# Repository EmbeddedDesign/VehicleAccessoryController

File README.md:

# VehicleAccessoryController
Vehicle Dash Cam and Accessory Controller

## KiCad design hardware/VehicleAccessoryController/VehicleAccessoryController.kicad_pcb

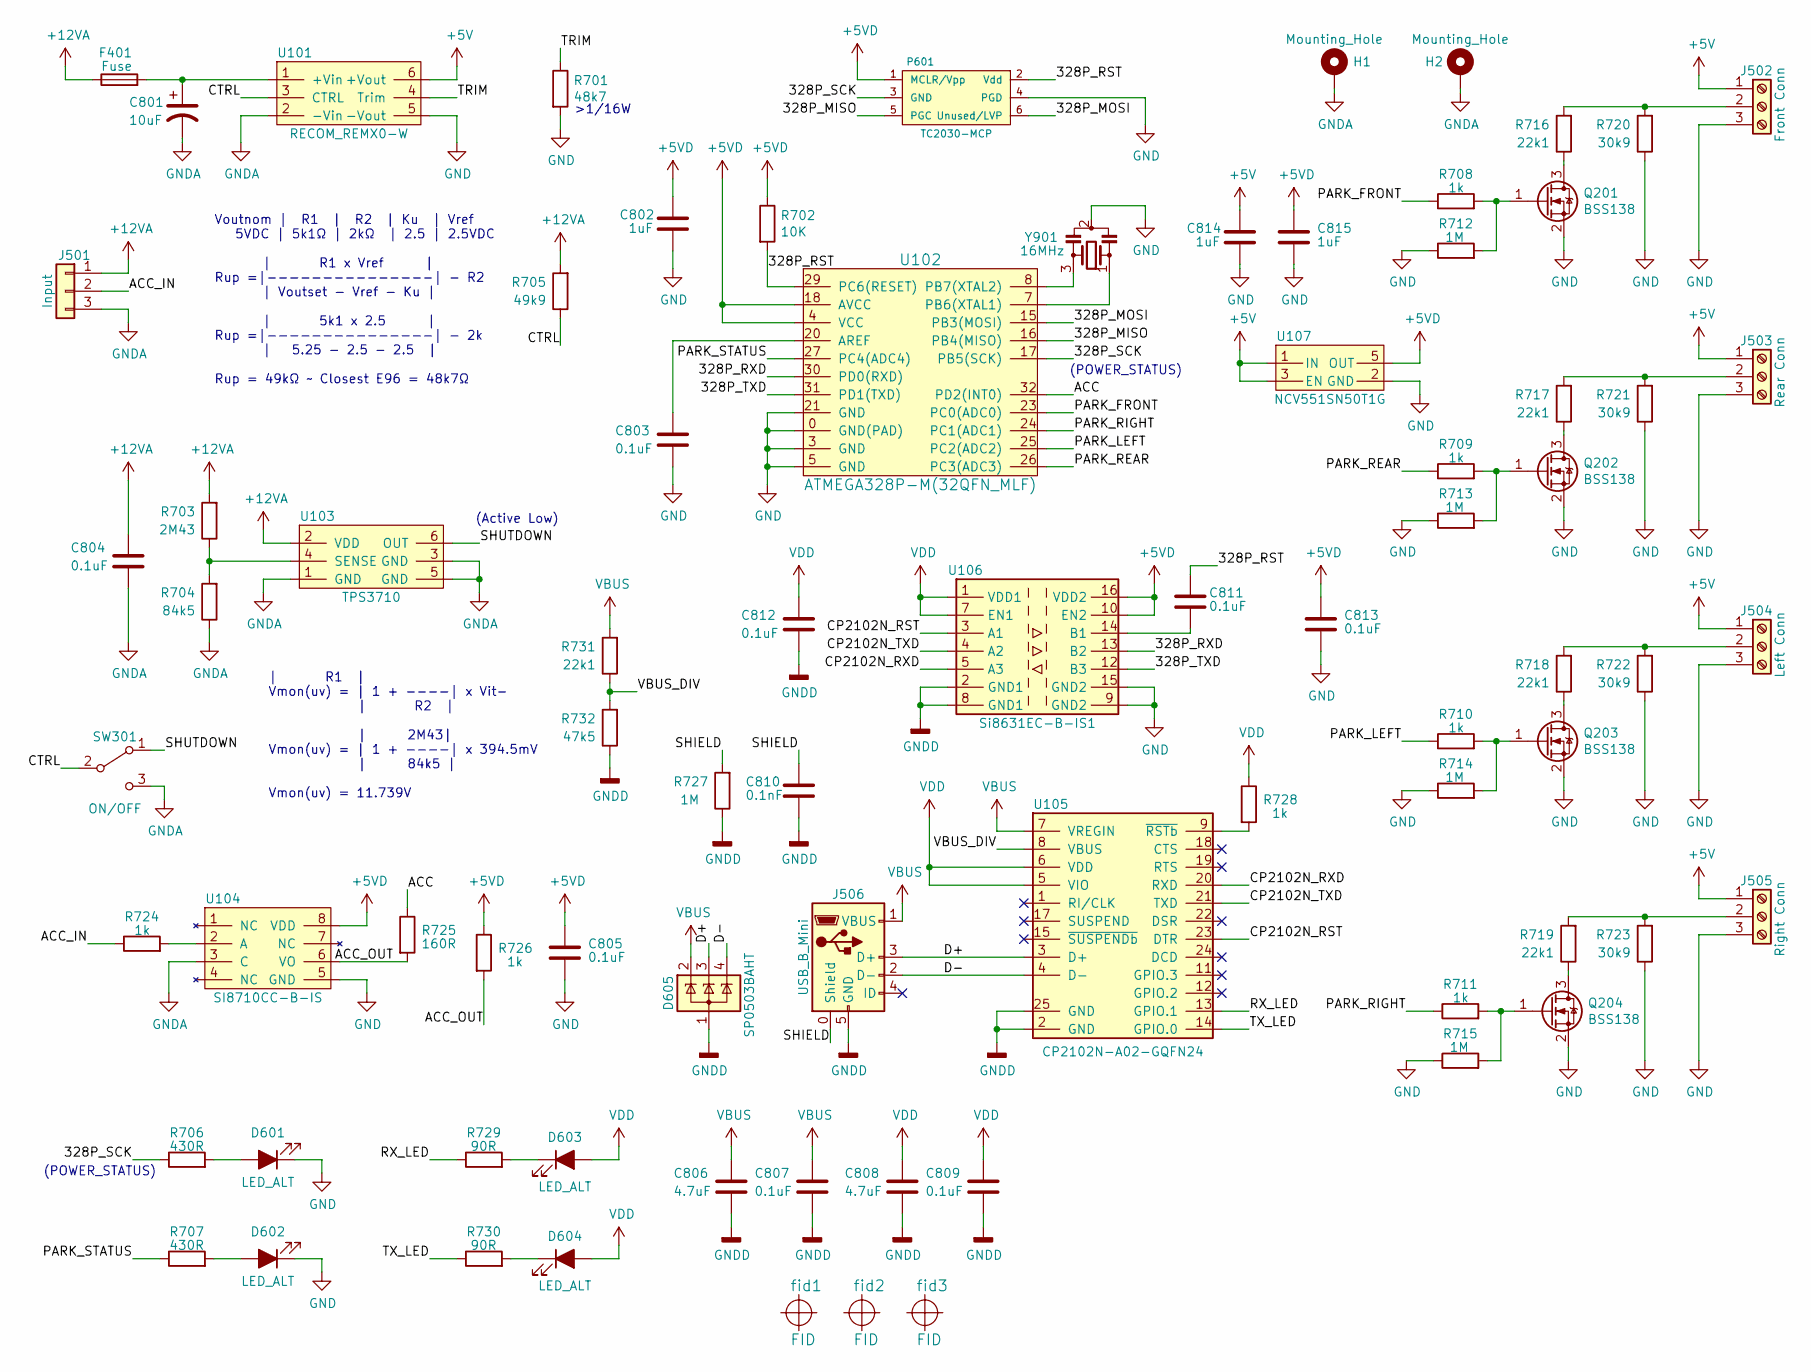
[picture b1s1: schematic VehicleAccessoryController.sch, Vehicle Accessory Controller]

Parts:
C801: 10uF; C_2917_D
C802, C814, C815: 1uF; C_0603
C803, C804, C805, C807, C809, C811, C812, C813: 0.1uF; C_0603
C806, C808: 4.7uF; C_0603
C810: 0.1nF; C_0603
D601, D602, D603, D604: LED_ALT; LED_0603
D605: SP0503BAHT; SOT-143
F401: Fuse; Keystone_3587
H1, H2: Mounting_Hole
J501: Input; Keystone_8719
J502: Front Conn; TE_1776275-3
J503: Rear Conn; TE_1776275-3
J504: Left Conn; TE_1776275-3
J505: Right Conn; TE_1776275-3
J506: USB_B_Mini; AFCI_10033526_USB-mini
P601: TC2030-MCP; TC2030_SMALL
Q201, Q202, Q203, Q204: BSS138; SOT-23
R701: 48k7; R_0603
R702: 10K; R_0603
R703: 2M43; R_0603
R704: 84k5; R_0603
R705: 49k9; R_0603
R706, R707: 430R; R_0603
R708, R709, R710, R711, R724, R726, R728: 1k; R_0603
R712, R713, R714, R715, R727: 1M; R_0603
R716, R717, R718, R719, R731: 22k1; R_0603
R720, R721, R722, R723: 30k9; R_0603
R725: 160R; R_0603
R729, R730: 90R; R_0603
R732: 47k5; R_0603
SW301: ON/OFF; C&K_ET_Series_Switch
U101: RECOM_REMX0-W; REM20-XXXXXW
U102: ATMEGA328P-M(32QFN_MLF); ATMEGA328P-MU_VQFN_MLF32
U103: TPS3710; TI_DSE_(S-PWSON-N6)
U104: SI8710CC-B-IS; SOIC-8_NB
U105: CP2102N-A02-GQFN24; QFN-24-1EP_4x4mm_P0.5mm_EP2.6x2.6mm
U106: Si8631EC-B-IS1; SOIC-16_3.9x9.9mm_P1.27mm
U107: NCV551SN50T1G; SOT-23-5
Y901: 16MHz; CSTNE_Resonator
fid1, fid2, fid3: FID; Fiducial

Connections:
+5V: C814.1, J502.1, J503.1, J504.1, J505.1, U101.6 (+Vout), U107.1 (IN), U107.3 (EN)
+5VD: C802.1, C805.1, C813.1, C815.1, P601.1 (MCLR/Vpp), R702.1, R726.1, U102.4 (VCC), U102.18 (AVCC), U104.8 (VDD), U106.10 (EN2), U106.16 (VDD2), U107.5 (OUT)
+12VA: C804.1, F401.1, J501.1, R703.2, R705.2, U103.2 (VDD)
/328P_MISO: P601.5 (PGC), U102.16 (PB4(MISO))
/328P_MOSI: P601.6 (Unused/LVP), U102.15 (PB3(MOSI))
/328P_RST: C811.1, P601.2 (Vdd), R702.2, U102.29 (PC6(RESET))
/328P_RXD: U102.30 (PD0(RXD)), U106.13 (B2)
/328P_SCK: P601.3 (GND), R706.1, U102.17 (PB5(SCK))
/328P_TXD: U102.31 (PD1(TXD)), U106.12 (B3)
/ACC: R725.1, U102.32 (PD2(INT0))
/ACC_IN: J501.2, R724.1
/ACC_OUT: R725.2, R726.2, U104.6 (VO)
/CP2102N_RST: U105.23 (DTR), U106.3 (A1)
/CP2102N_RXD: U105.20 (RXD), U106.5 (A3)
/CP2102N_TXD: U105.21 (TXD), U106.4 (A2)
/CTRL: R705.1, SW301.2 (B), U101.3 (CTRL)
/D+: D605.3 (K), J506.3 (D+), U105.3 (D+)
/D-: D605.4 (K), J506.2 (D-), U105.4 (D-)
/PARK_FRONT: R708.1, U102.23 (PC0(ADC0))
/PARK_LEFT: R710.1, U102.25 (PC2(ADC2))
/PARK_REAR: R709.1, U102.26 (PC3(ADC3))
/PARK_RIGHT: R711.1, U102.24 (PC1(ADC1))
/PARK_STATUS: R707.1, U102.27 (PC4(ADC4))
/RX_LED: R729.1, U105.13 (GPIO.1)
/SHIELD: C810.1, J506.0 (Shield), R727.2
/SHUTDOWN: SW301.1 (A), U103.6 (OUT)
/TRIM: R701.1, U101.4 (Trim)
/TX_LED: R730.1, U105.14 (GPIO.0)
/VBUS_DIV: R731.1, R732.2, U105.8 (VBUS)
GND: C802.2, C803.2, C805.2, C813.2, C814.2, C815.2, D601.1 (K), D602.1 (K), J502.3, J503.3, J504.3, J505.3, P601.4 (PGD), Q201.2 (S), Q202.2 (S), Q203.2 (S), Q204.2 (S), R701.2, R712.1, R713.1, R714.1, R715.1, R720.1, R721.1, R722.1, R723.1, U101.5 (-Vout), U102.0 (GND(PAD)), U102.3 (GND), U102.5 (GND), U102.21 (GND), U104.5 (GND), U106.9 (GND2), U106.15 (GND2), U107.2 (GND), Y901.2
GNDA: C801.2, C804.2, H1.1, H2.1, J501.3, R704.1, SW301.3 (C), U101.2 (-Vin), U103.1 (GND), U103.3 (GND), U103.5 (GND), U104.3 (C)
GNDD: C806.2, C807.2, C808.2, C809.2, C810.2, C812.2, D605.1 (A), J506.5 (GND), R727.1, R732.1, U105.2 (GND), U105.25 (GND), U106.2 (GND1), U106.8 (GND1)
unnamed: C801.1, F401.2, U101.1 (+Vin)
unnamed: C803.1, U102.20 (AREF)
unnamed: C811.2, U106.14 (B1)
unnamed: D601.2 (A), R706.2
unnamed: D602.2 (A), R707.2
unnamed: D603.1 (K), R729.2
unnamed: D604.1 (K), R730.2
unnamed: J502.2, R716.2, R720.2
unnamed: J503.2, R717.2, R721.2
unnamed: J504.2, R718.2, R722.2
unnamed: J505.2, R719.2, R723.2
unnamed: Q201.1 (G), R708.2, R712.2
unnamed: Q201.3 (D), R716.1
unnamed: Q202.1 (G), R709.2, R713.2
unnamed: Q202.3 (D), R717.1
unnamed: Q203.1 (G), R710.2, R714.2
unnamed: Q203.3 (D), R718.1
unnamed: Q204.1 (G), R711.2, R715.2
unnamed: Q204.3 (D), R719.1
unnamed: R703.1, R704.2, U103.4 (SENSE)
unnamed: R724.2, U104.2 (A)
unnamed: R728.2, U105.9 (~RSTb)
unnamed: U102.7 (PB6(XTAL1)), Y901.1
unnamed: U102.8 (PB7(XTAL2)), Y901.3
VBUS: C806.1, C807.1, D605.2 (K), J506.1 (VBUS), R731.2, U105.7 (VREGIN)
VDD: C808.1, C809.1, C812.1, D603.2 (A), D604.2 (A), R728.1, U105.5 (VIO), U105.6 (VDD), U106.1 (VDD1), U106.7 (EN1)

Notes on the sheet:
Voutnom | R1 | R2 | Ku | Vref 5VDC | 5k1Ω | 2kΩ | 2.5 | 2.5VDC | R1 x Vref | Rup =|---------------| - R2 | Voutset - Vref - Ku | | 5k1 x 2.5 | Rup =|---------------| - 2k | 5.25 - 2.5 - 2.5 | Rup = 49kΩ ~~ Closest E96 = 48k7Ω
>1/16W
(Active Low)
| R1 | Vmon(uv) = | 1 + ----| x Vit- | R2 | | 2M43| Vmon(uv) = | 1 + ----| x 394.5mV | 84k5 | Vmon(uv) = 11.739V
(POWER_STATUS)

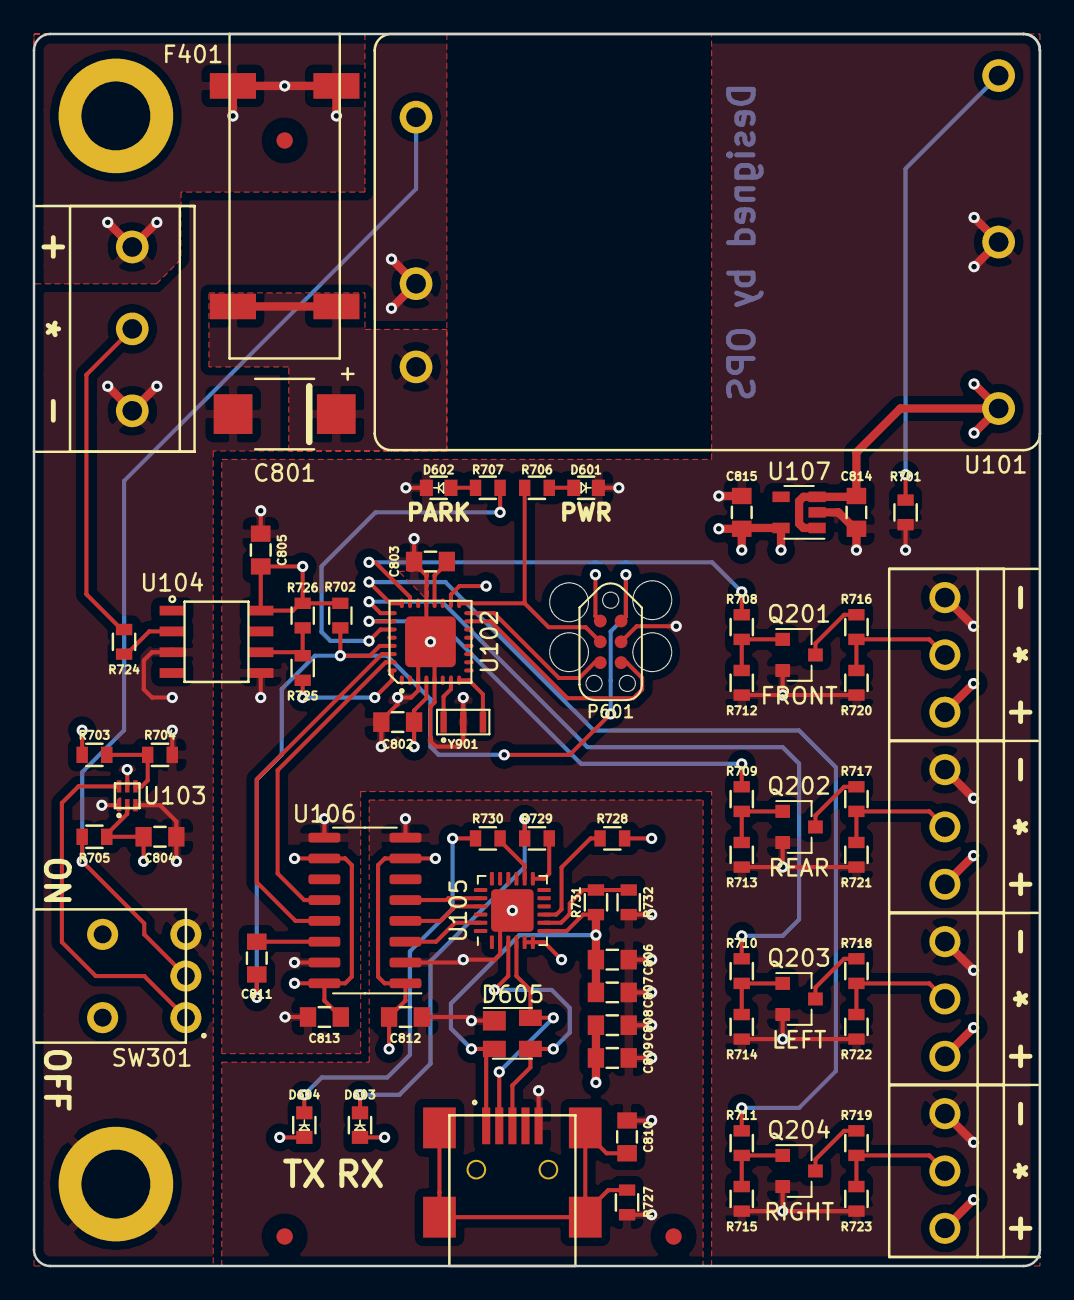
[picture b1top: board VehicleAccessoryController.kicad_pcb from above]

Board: 4 copper layers, 61.4 x 75.2 mm, 78 parts (0 on the bottom side), 58 nets.

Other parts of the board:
fidr: FID; Fiducial

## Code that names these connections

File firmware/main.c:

/*
 * Vehicle Accessory Controller
 *
 */

 // Include headers
#include <avr/power.h>
#include <avr/sleep.h>
#include <avr/interrupt.h>
#include <stdio.h>
#include "main.h"
#include "uart.h"

// Pin definitions
#define PARK_FRONT   14 // A0
#define PARK_RIGHT   15 // A1
#define PARK_LEFT    16 // A2
#define PARK_REAR    17 // A3
#define PARK_STATUS  18
#define POWER_STATUS 13
#define ACC          2

// Enable Park Mode
void enableParkMode(void) {
  PORTC &= ~_BV(PORTC0); // digitalWrite(PARK_FRONT, LOW);
  PORTC &= ~_BV(PORTC1); // digitalWrite(PARK_RIGHT, LOW);
  PORTC &= ~_BV(PORTC2); // digitalWrite(PARK_LEFT, LOW);
  PORTC &= ~_BV(PORTC3); // digitalWrite(PARK_REAR, LOW);
  // Turn PARK_STATUS LED ON
  PORTC |= _BV(PORTC4); // digitalWrite(PARK_STATUS, HIGH);
  puts("Park Mode: Enabled"); // Print park mode status message
}

// Disable Park Mode
void disableParkMode(void) {
  PORTC |= _BV(PORTC0); // digitalWrite(PARK_FRONT, HIGH);
  PORTC |= _BV(PORTC1); // digitalWrite(PARK_RIGHT, HIGH);
  PORTC |= _BV(PORTC2); // digitalWrite(PARK_LEFT, HIGH);
  PORTC |= _BV(PORTC3); // digitalWrite(PARK_REAR, HIGH);
  // Turn PARK_STATUS LED OFF
  PORTC &= ~_BV(PORTC4); // digitalWrite(PARK_STATUS, LOW);
  puts("Park Mode: Disabled"); // Print park mode status message
}

// Main loop
int main(void) {
  // Configure IO
  DDRC |= _BV(DDC0);    // pinMode(PARK_FRONT, OUTPUT);
  DDRC |= _BV(DDC1);    // pinMode(PARK_RIGHT, OUTPUT);
  DDRC |= _BV(DDC2);    // pinMode(PARK_LEFT, OUTPUT);
  DDRC |= _BV(DDC3);    // pinMode(PARK_REAR, OUTPUT);
  DDRC |= _BV(DDC4);    // pinMode(PARK_STATUS, OUTPUT);
  DDRB |= _BV(DDB5);    // pinMode(POWER_STATUS, OUTPUT);
  DDRD &= ~_BV(DDD2);   // Clear the PD2 pin
  PORTD |= _BV(PORTD2); // Enable PD2 internal pull-up
  
  // UART setup
  uart_init();
  stdout = &uart_output;
  stdin  = &uart_input;

  // Turn POWER_STATUS LED ON
  PORTB |= _BV(PORTB5); // digitalWrite(POWER_STATUS, HIGH);
  // Print system status message
  puts("System Status: OK");
 
 // Loop
  while(1) {
    // Power saving
    power_adc_disable ();
    power_spi_disable();
    power_twi_disable();
    power_timer1_disable();
    power_timer2_disable();

    // Configure sleep
    set_sleep_mode(SLEEP_MODE_PWR_DOWN);
    sleep_enable();

    // Do not interrupt before to sleep or ISR will detach interrupts won't wake.
    cli();

    // Interrupt init
    // Enable Pin Change Interrupt on the PCINT18 pin using Pin Change Mask Register 2 (PCMSK2)
    PCMSK2 |= _BV(PCINT18);
    // Enable Pin Change Interrupt 2 using the Pin Change Interrupt Control Register (PCICR)
    PCICR |= _BV(PCIE2);

    // Turn off brown-out enable in software
    MCUCR = _BV(BODS) | _BV(BODSE);
    MCUCR = _BV(BODS);

    // Enable interrupts
    sei();
    // Guaranteed sleep_cpu call will be done as CPU executes next instruction after interrupts enabled
    sleep_cpu();
  }

  return 0;
}

ISR(PCINT2_vect)
{
  // Cancel sleep as a precaution
  sleep_disable();
  // Disable Pin Change Interrupt 2 while we do other stuff
  PCICR &= ~_BV(PCIE2);
  // Read PD2 using the Port D Pin Input Register (PIND)
  if (PIND & _BV(PIND2)) { // PD2 is HIGH
    enableParkMode();
  } else { // PD2 is LOW
    disableParkMode();
  }
}

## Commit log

2019-10-24 Schematic additions
2019-10-30 Schematic updates
2019-11-08 add test board
2019-11-15 test board layout
2019-11-16 test board schematic/layout updates, gerbers
2019-11-17 BOM update, change output connectors
2019-11-20 schematic updates, begin layout
2019-11-21 add parts still required for build doc
2019-11-22 test board PDFs, label updates, merge duplicates on BOMs
2019-11-23 updated required parts for test board list
2019-11-23 shcematic updates
2019-11-30 correct fuse holder, ACC pull-up, BOM Accessories, create firmware dir
2019-11-30 adjust reference text size, fab notes
2019-12-01 test board code
2019-12-01 firmware updates
2019-12-03 layout updates
2020-06-09 CAD models update
2020-06-13 CAD path update, add fuse CAD, add images
2020-06-14 BOM accessory updates
2020-06-22 layout and cad updates
2020-06-23 layout and cad updates, add schematic pdf
2020-06-24 layout and firmware updates
2020-06-24 add .gitignore
2020-06-24 schematic/layout updates
2020-06-26 layout updates, gerbers
2020-06-28 layout updates, gerbers, pdfs
2020-07-01 project file update
2020-07-04 CAD path update
2020-07-08 add custom cp2102n driver, directory cleanup
2020-07-08 update pdf, custom cp2102n driver code, avr updates
2020-07-10 store Strings in flash, Linux driver install instructions, directory cleanup
2020-07-10 update custom cp2010n configuration files
2020-07-10 add CAD image
2020-07-12 add default park mode state
2020-07-13 update main code
